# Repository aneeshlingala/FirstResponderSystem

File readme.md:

### Tech Report Link: [https://github.com/aneeshlingala/FirstResponderSystem/blob/main/tech_report_reverie_hacks_final.pdf](https://github.com/aneeshlingala/FirstResponderSystem/blob/main/tech_report_reverie_hacks_final.pdf)

# PROBLEM
During major disasters, first responders (police, fire, medical) do not have a reliable way to track their environment, find survivors, and receive information in real time. Existing systems can be expensive, hard to deploy, or require additional personnel to operate, wasting manpower that can be used from more urgent tasks.

# SOLUTION
The FirstResponderSystem uses cheap to manufacture, durable, and easy-to-deploy custom-made PCBs that create a centralized long-range radio network suited for emergencies instead of relying on broken or buggy connection systems (WiFi, Mobile Data, etc). By providing real-time sensor data and survivor detection, FirstResponderSystem allows emergency personnel to analyze dangerous conditions, locate any survivors, and make safe decisions while allowing responders to work on more urgent things. The data can also be sent to other organizations to relay information to people in the area, declare evacuations/emergencies, and more. The survivor node can be put in rubble to detect survivors, while the environmental node can be put in various parts of the disaster area. Multiple survivor and environmental nodes can be used at once. 

# CONTENTS OF GITHUB REPO
1. Survivor PCB
   * This PCB utilizes the cheap ATTINY16-14 MCU and utilizes Doppler Radars, Distance Sensors, and Infrared cameras to detect survivors trapped under rubble or other items. It broadcasts its data using an RFM95W LoRa transceiver (receiver and transmitter) on 915mHz. It is battery powered and uses a u.FL port for the antenna.

2. Environmental PCB
   * This PCB utilizes the cost-friendly ESP32 MCU and uses Bosch BME280 and BME680 Sensors to capture data about the environment. It also uses AQI, VOC, and other environmental sensors. It broadcasts its data using an RFM95W LoRa module on 915mHz, with a u.FL antenna port. It is battery powered.

3. Broadcast PCB
   * This PCB uses the cheap ATTINY16-14 MCU and receives data from the other two PCBS using the RFM95W LoRa transceiver. It takes the information received and sends it over Serial on Micro-USB to a computer to read. It is powered by the Micro-USB port.

4. Computer Software
   * The computer software includes a .py file for universal execution, as well as a .exe file generated by py2exe for quick use. The software is able to detect packets sent by the Broadcast PCB over serial and has an interface to select the COM port to read from. Once detected, it lists all the PCBS and shows info if you click on the names of the PCBS. It classifies the PCB as either ENV (environmental) or SRV (survivor detection). It shows all the info recorded by both PCBS. There is also a DEMO mode, which populates the user interface with "fake" broadcasting PCBS for showing at events or getting used to the interface.
  
# INFO

The PCBS were made in KiCAD 10 with footprints and symbols from LCSC, bundled KiCAD files, and SnapEDA.

All of the PCBS come with images:
* Image of the schematic
* Image of the PCB top-down
* Image of the PCB in 3D view

All of the PCBS come with code made in PlatformIO in VSCode. The programming language used to make the code is C++. The code successfully compiles with the firmware file in the .pio/build/[MCU NAME]/ and uses a good amount of 3rd-party libraries to interface with various components. 

The folders inside the survivornode, broadcastnode, or environmental node are structured as follows:
* The pcb_code folder includes the PCB Code written in C++.
* The pcb_images folder includes images of the schematic, PCB top-down, and the PCB in 3D.
* The pcb_data folder includes KiCAD files for opening the PCB in KiCAD. It also includes the Bill of Materials (BOM) and component positions CSV as well as the Gerber files in a zip.

The computer_code folder has a reciever.exe file for running on Windows without any dependencies being required to be installed. The reciever.py file can be run universally and requires Tkinter (already installed on most Python distributions), pyserial, and Python 3.13+ to run.

# WHAT I LEARNED
I learned how to make PCBs in KiCad 10 with proper symbols and footprints. I also learned how to use the design and electrical rules checker to make sure my project met all of the rules.

# CHALLENGES I FACED
Some challenges I faced included having issues with footprint/symbol quality, finding proper footprints for some of my component choices, and exporting gerbers. I solved these issues by searching up solutions online and using external plugins to export gerbers properly since it was bugged out with LCSC symbols. 

# DIAGRAM

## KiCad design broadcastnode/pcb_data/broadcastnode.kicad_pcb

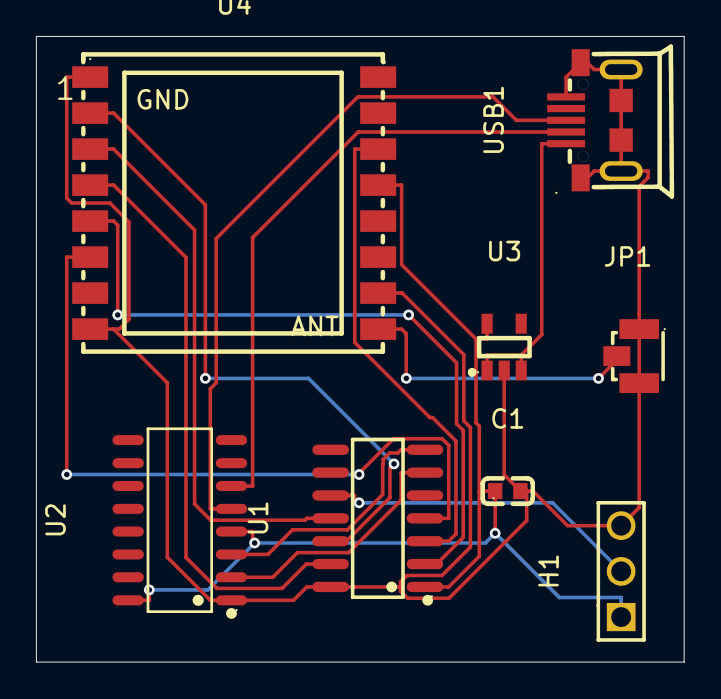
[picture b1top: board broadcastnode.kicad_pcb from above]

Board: 2 copper layers, 36.0 x 34.8 mm, 8 parts (0 on the bottom side), 15 nets.

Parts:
C1: CC0603KRX7R9BB104; C0603
H1: Header-Male-2.54_1x3; HDR-TH_3P-P2.54-V-M-1
JP1: U.FL-R-SMT-1; ANT-SMD_UFL-R-SMT-1-10
U1: ATTINY1614-SSNR; SOIC-14_L8.7-W3.9-P1.27-LS6.0-BL
U2: CH340C; SOP-16_L10.0-W3.9-P1.27-LS6.0-BL
U3: AP2112K-3.3TRG1; SOT-25-5_L2.9-W1.6-P0.95-LS2.8-BL
U4: RFM95W-915S2; WIRELM-SMD_16P-L16.0-W16.0-P2.00_LORA-CC68-915MHZ-TCXO
USB1: MICRO5.9MMUSB; MICRO-USB-SMD_5P-P0.65-H-F_MICRO5.9MMUSB

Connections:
unnamed: JP1.2 (SIN), U4.9 (ANT)
unnamed: C1.2, H1.3, JP1.1 (GND), JP1.3 (GND), U1.14 (GND), U2.1 (GND), U3.2 (GND), U4.1 (GND), U4.8 (GND), U4.10 (GND), USB1.5 (GND), USB1.6
unnamed: H1.2, U1.10 (PA0/#RESET/UPDI)
unnamed: U1.11 (PA1), U4.3 (MOSI)
unnamed: U1.12 (PA2), U4.2 (MISO)
unnamed: U1.13 (PA3/EXTCLK), U4.4 (SCK)
unnamed: U1.2 (PA4), U4.5 (NSS)
unnamed: U1.3 (PA5), U4.14 (DIO0)
unnamed: U1.4 (PA6), U4.6 (RESET)
unnamed: U1.6 (TOSC1/PB3), U2.2 (TXD)
unnamed: U1.7 (TOSC2/PB2), U2.3 (RXD)
unnamed: C1.1, H1.1, U1.1 (VDD), U2.4 (V3), U2.16 (VCC), U3.5 (VOUT), U4.13 (3.3V)
unnamed: U2.5 (D+), USB1.3 (D+)
unnamed: U2.6 (D-), USB1.2 (D-)
unnamed: U3.1 (VIN), U3.3 (EN), USB1.1 (VBUS)

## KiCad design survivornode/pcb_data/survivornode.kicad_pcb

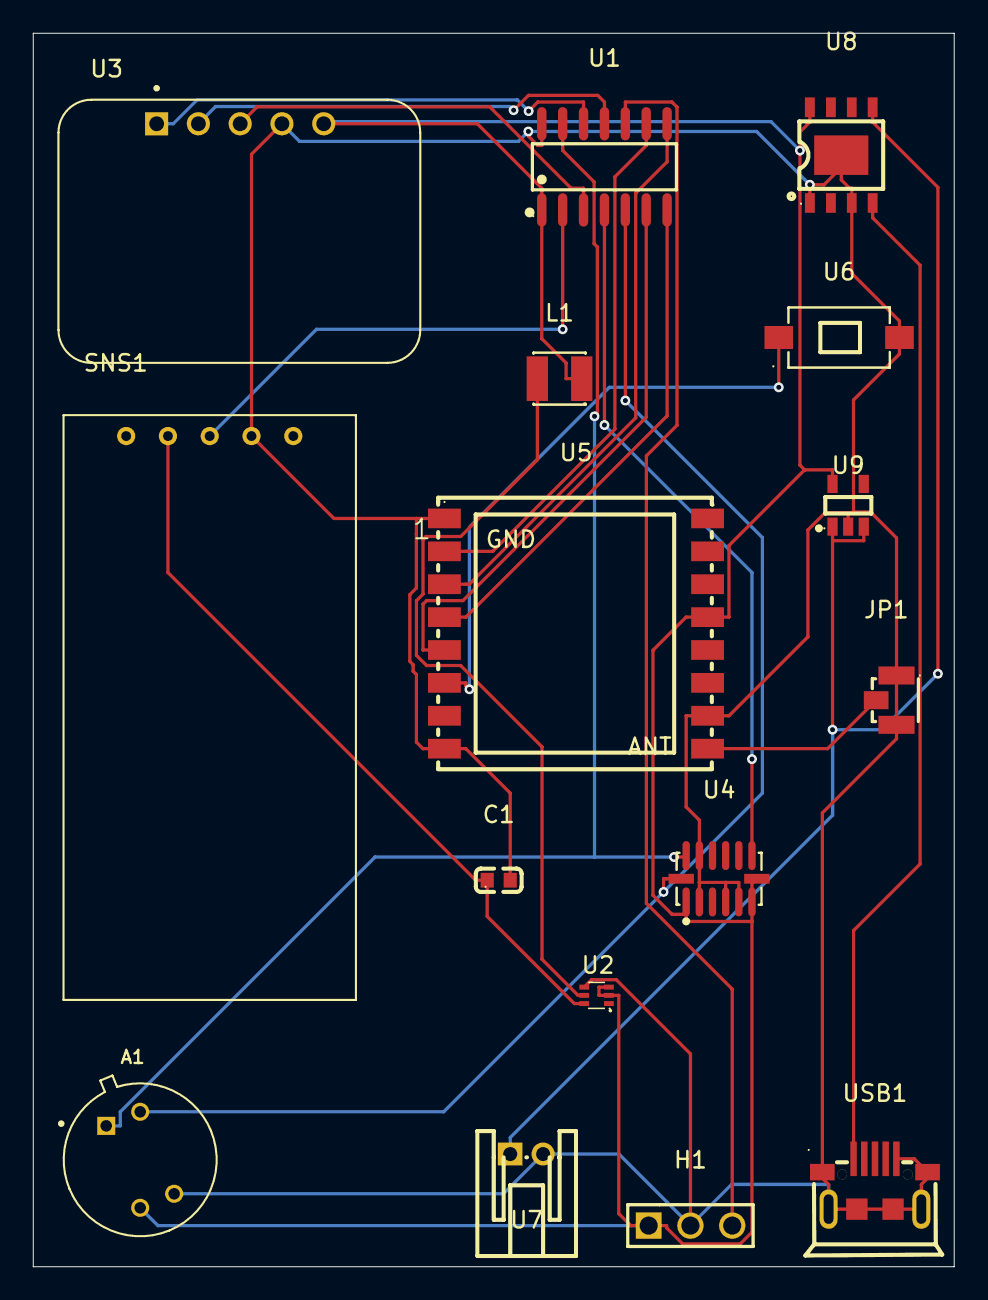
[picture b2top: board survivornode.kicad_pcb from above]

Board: 2 copper layers, 56.0 x 75.0 mm, 16 parts (0 on the bottom side), 20 nets.

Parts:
A1: MLX90640ESF-BAA-000-TU; TO292P930H600-4
C1: CL10A105KB8NNNC; C0603
H1: Header-Male-2.54_1x3; HDR-TH_3P-P2.54-V-M-1
JP1: U.FL-R-SMT-1; ANT-SMD_UFL-R-SMT-1-10
L1: FNR3015S2R2MT; IND-SMD_L3.0-W3.0_FNR30XXS
SNS1: RCWL-0516
U1: ATTINY1614-SSNR; SOIC-14_L8.7-W3.9-P1.27-LS6.0-BL
U2: TPS61023DRLR; SOT-563_L1.6-W1.2-P0.50-LS1.6-BR
U3: HLK-LD2410C; MODULE_HLK-LD2410C
U4: ADXL345BCCZ-RL7; LGA-14_L5.0-W3.0-P0.80-BL
U5: RFM95W-915S2; WIRELM-SMD_16P-L16.0-W16.0-P2.00_LORA-CC68-915MHZ-TCXO
U6: YZA-032-5.0W; SW-SMD_L6.0-W3.5-LS8.0
U7: S2B-PH-K-S; CONN-TH_S2B-PH-K-S-LF-SN
U8: TP4056; ESOP-8_L4.9-W3.9-P1.27-LS6.0-BL-EP
U9: AP2112K-3.3TRG1; SOT-25-5_L2.9-W1.6-P0.95-LS2.8-BL
USB1: MICRO5.9MMUSB; MICRO-USB-SMD_5P-P0.65-H-F_MICRO5.9MMUSB

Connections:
unnamed: A1.3 (GND), C1.2, H1.2, JP1.1 (GND), JP1.3 (GND), SNS1.GND, U1.14 (GND), U2.4 (GND), U3.4 (GND), U4.2 (GND), U4.4 (GND), U4.5 (GND), U4.12 (SDO/ALTADDRESS), U5.1 (GND), U5.8 (GND), U5.10 (GND), U6.2, U7.2, U8.1 (TEMP), U8.3 (GND), U8.9 (EP), U9.2 (GND), USB1.5 (GND), USB1.6
unnamed: A1.4 (SCL), U1.5 (PA7), U4.14 (SCL/SCLK)
unnamed: A1.1 (SDA), U1.13 (PA3/EXTCLK), U4.13 (SDA/SDI/SDIO)
unnamed: A1.2 (VDD), H1.1, L1.1, U1.1 (VDD), U2.2 (EN), U2.3 (VIN), U3.5 (VCC), U4.1 (VDDIO), U4.6 (VS), U4.7 (~CS), U5.13 (3.3V), U8.8 (CE), U9.5 (VOUT)
unnamed: JP1.2 (SIN), U5.9 (ANT)
unnamed: H1.3, U1.10 (PA0/#RESET/UPDI)
unnamed: U1.11 (PA1), U3.2 (UART_RX)
unnamed: U1.12 (PA2), U3.1 (UART_TX)
unnamed: SNS1.OUT, U1.2 (PA4)
unnamed: U1.3 (PA5), U3.3 (OUT)
unnamed: U1.4 (PA6), U4.8 (INT1)
unnamed: U1.9 (PB0), U5.2 (MISO)
unnamed: U1.8 (PB1), U5.3 (MOSI)
unnamed: U1.6 (TOSC1/PB3), U5.5 (NSS)
unnamed: U1.7 (TOSC2/PB2), U5.4 (SCK)
unnamed: L1.2, U2.5 (SW)
unnamed: C1.1, SNS1.VIN, U2.6 (VOUT)
unnamed: U5.6 (RESET), U6.1
unnamed: U7.1, U8.5 (BAT), U9.1 (VIN), U9.3 (EN)
unnamed: U8.4 (VCC), USB1.1 (VBUS)

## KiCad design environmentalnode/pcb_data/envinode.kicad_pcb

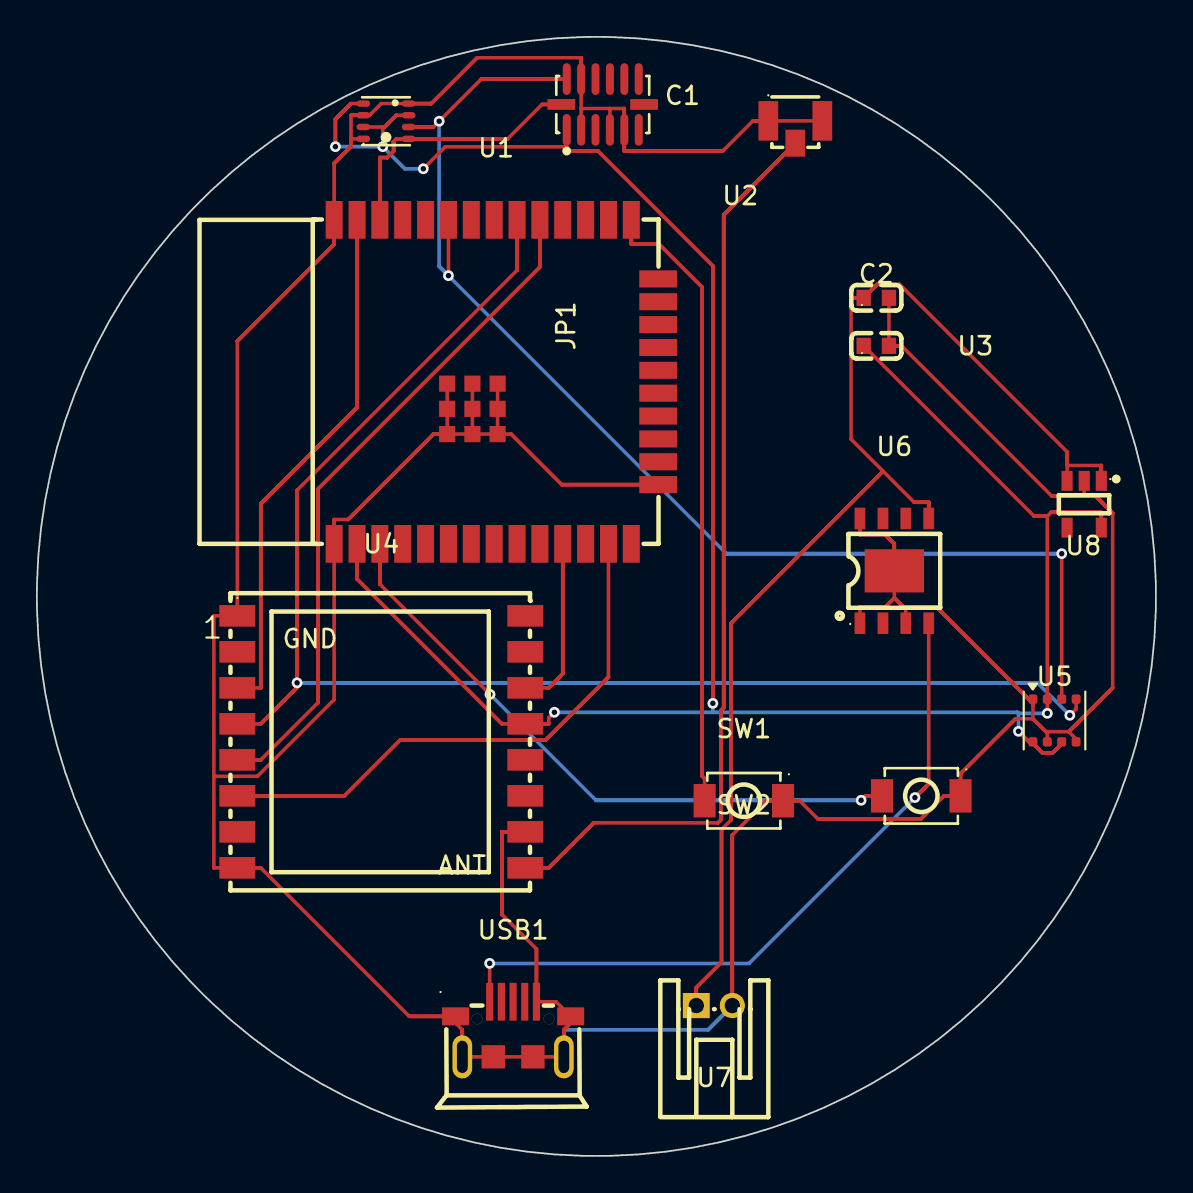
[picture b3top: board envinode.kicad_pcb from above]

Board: 2 copper layers, 62.2 x 62.2 mm, 14 parts (0 on the bottom side), 15 nets.

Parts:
C1: CC0603KRX7R9BB104; C0603
C2: CL10A105KB8NNNC; C0603
JP1: U.FL-R-SMT-1; ANT-SMD_UFL-R-SMT-1-10
SW1, SW2: TS-1088-AR02016; SW-SMD_L3.9-W3.0-P4.45
U1: ESP32-WROOM-32E; WIFI-SMD_ESP32-WROOM-32E
U2: BME280; LGA-8_BME280_BL
U3: ADXL345BCCZ-RL7; LGA-14_L5.0-W3.0-P0.80-BL
U4: RFM95W-915S2; WIRELM-SMD_16P-L16.0-W16.0-P2.00_LORA-CC68-915MHZ-TCXO
U5: BME680; Bosch_LGA-8_3x3mm_P0.8mm_ClockwisePinNumbering
U6: TP4056; ESOP-8_L4.9-W3.9-P1.27-LS6.0-BL-EP
U7: S2B-PH-K-S; CONN-TH_S2B-PH-K-S-LF-SN
U8: AP2112K-3.3TRG1; SOT-25-5_L2.9-W1.6-P0.95-LS2.8-BL
USB1: MICRO5.9MMUSB; MICRO-USB-SMD_5P-P0.65-H-F_MICRO5.9MMUSB

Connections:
unnamed: JP1.2 (SIN), U4.9 (ANT)
unnamed: C2.1, U1.2 (3V3), U2.2 (CSB), U2.6 (VDDIO), U2.8 (VDD), U3.1 (VDDIO), U4.13 (3.3V), U5.2 (CSB), U5.5 (SDO), U5.6 (VDDIO), U5.8 (VDD), U8.5 (VOUT)
unnamed: SW2.1, U1.3 (EN)
unnamed: SW1.1, U1.25 (IO0)
unnamed: U1.29 (IO5), U4.5 (NSS)
unnamed: U1.13 (IO14), U4.6 (RESET)
unnamed: U1.30 (IO18), U4.4 (SCK), U5.4 (SCK)
unnamed: U1.31 (IO19), U4.2 (MISO)
unnamed: U1.33 (IO21), U2.3 (SDI), U3.13 (SDA/SDI/SDIO), U5.3 (SDI)
unnamed: U1.36 (IO22), U2.4 (SCK), U3.14 (SCL/SCLK)
unnamed: U1.37 (IO23), U4.3 (MOSI)
unnamed: U1.11 (IO26), U4.14 (DIO0)
unnamed: C1.2, C2.2, JP1.1 (GND), JP1.3 (GND), SW1.2, SW2.2, U1.1 (GND), U1.15 (GND), U1.38 (GND), U1.39 (GND), U2.1 (GND), U2.5 (SDO), U2.7 (GND), U3.2 (GND), U3.4 (GND), U3.5 (GND), U3.12 (SDO/ALTADDRESS), U4.1 (GND), U4.8 (GND), U4.10 (GND), U5.1 (GND), U5.7 (GND), U6.1 (TEMP), U6.3 (GND), U6.8 (CE), U6.9 (EP), U7.2, U8.2 (GND), USB1.5 (GND), USB1.6
unnamed: C1.1, U6.5 (BAT), U7.1, U8.1 (VIN), U8.3 (EN)
unnamed: U6.4 (VCC), USB1.1 (VBUS)
